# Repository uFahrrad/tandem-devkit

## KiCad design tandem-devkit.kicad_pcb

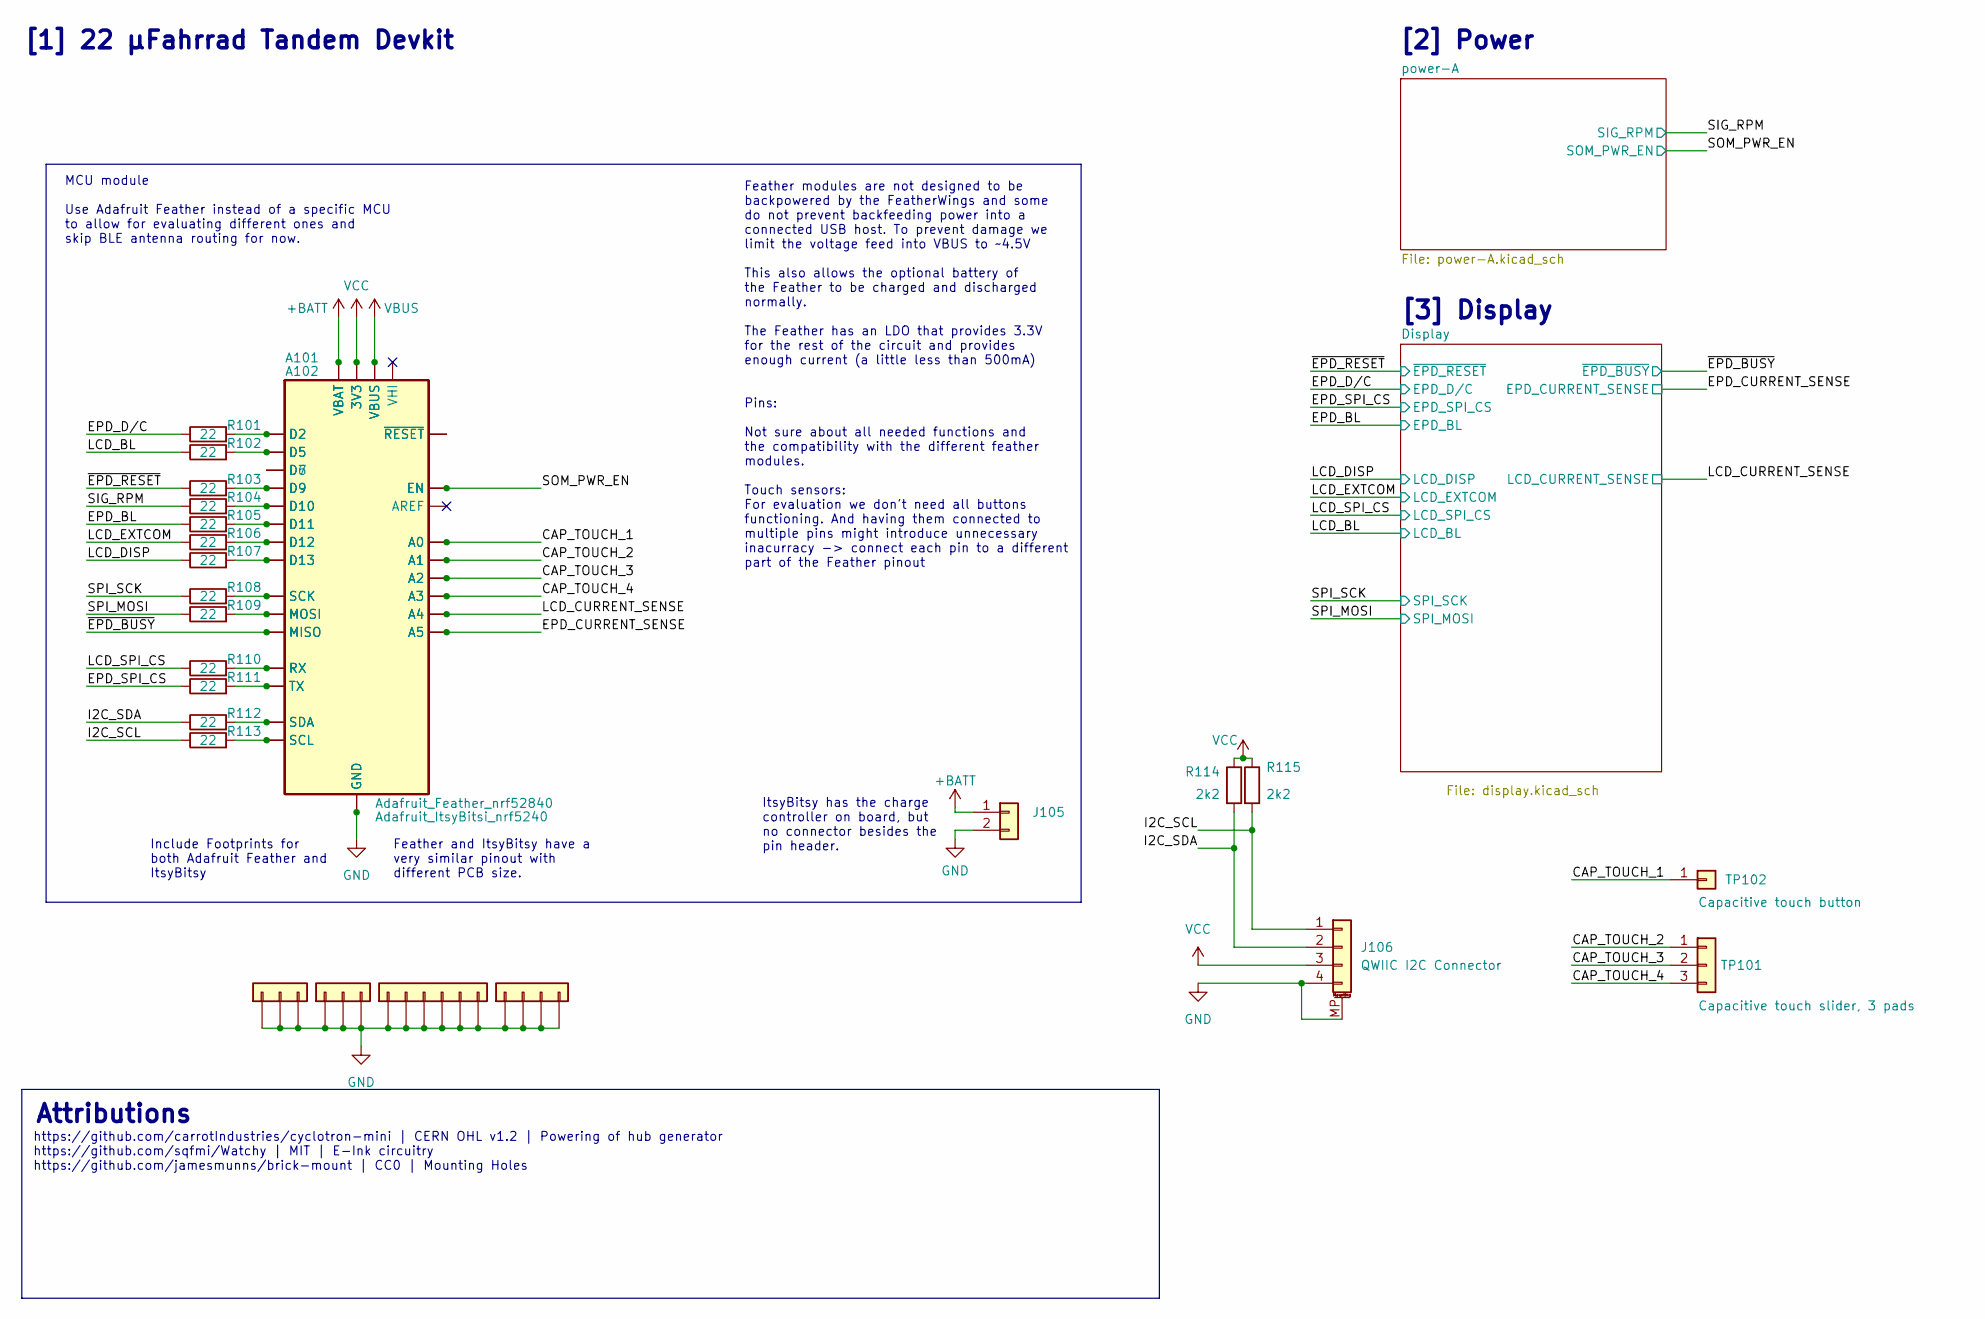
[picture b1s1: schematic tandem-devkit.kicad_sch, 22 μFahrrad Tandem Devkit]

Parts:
A101: Adafruit_ItsyBitsi_nrf5240; Adafruit_ItsyBitsy-nrf52840
A102: Adafruit_Feather_nrf52840; Adafruit_Feather
J101, J102: Conn_01x03; brick-1x3
J103: Conn_01x06; brick-1x6
J104: Conn_01x04; brick-2x2
J105: Conn_01x02; JST_PH_B2B-PH-K_1x02_P2.00mm_Vertical; JLCPCB C173752
J106: QWIIC I2C Connector; JST_SHL_SM04B-SHLS-TF_1x04-1MP_P1.00mm_Horizontal; JLCPCB C145956
R101, R102, R103, R104, R105, R106, R107, R108, R109, R110, R111, R112, R113: 22; R_0603_1608Metric; LCSC C23345
R114, R115: 2k2; R_0603_1608Metric; LCSC C4190
TP101: Capacitive touch slider, 3 pads; TouchSlider-3_30x13mm-covered
TP102: Capacitive touch button; CapBtn_Board_edge

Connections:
+BATT: A101.28 (VBAT), A102.28 (VBAT), J105.1
/CAP_TOUCH_1: A101.5 (A0), A102.5 (A0), TP102.1
/CAP_TOUCH_2: A101.6 (A1), A102.6 (A1), TP101.1; also elsewhere on the board
/CAP_TOUCH_3: A101.7 (A2), A102.7 (A2), TP101.2; also elsewhere on the board
/CAP_TOUCH_4: A101.8 (A3), A102.8 (A3), TP101.3; also elsewhere on the board
/EPD_BL: R105.1; also elsewhere on the board
/EPD_CURRENT_SENSE: A101.10 (A5), A102.10 (A5); also elsewhere on the board
/EPD_D/C: R101.1; also elsewhere on the board
/EPD_SPI_CS: R111.1; also elsewhere on the board
/I2C_SCL: J106.1, R113.1, R115.2
/I2C_SDA: J106.2, R112.1, R114.2
/LCD_BL: R102.1; also elsewhere on the board
/LCD_CURRENT_SENSE: A101.9 (A4), A102.9 (A4); also elsewhere on the board
/LCD_DISP: R107.1; also elsewhere on the board
/LCD_EXTCOM: R106.1; also elsewhere on the board
/LCD_SPI_CS: R110.1; also elsewhere on the board
/SIG_RPM: R104.1; also elsewhere on the board
/SOM_PWR_EN: A101.3 (EN), A102.27 (EN); also elsewhere on the board
/SPI_MOSI: R109.1; also elsewhere on the board
/SPI_SCK: R108.1; also elsewhere on the board
/~EPD_BUSY: A101.13 (MISO), A102.13 (MISO); also elsewhere on the board
/~EPD_RESET: R103.1; also elsewhere on the board
GND: A101.27 (GND), A102.4 (GND), J101.1, J101.2, J101.3, J102.1, J102.2, J102.3, J103.1, J103.2, J103.3, J103.4, J103.5, J103.6, J104.1, J104.2, J104.3, J104.4, J105.2, J106.4, J106.MP (MountPin); also elsewhere on the board
unnamed: A101.1 (~RESET), A102.1 (~RESET)
unnamed: A101.11 (SCK), A102.11 (SCK), R108.2
unnamed: A101.12 (MOSI), A102.12 (MOSI), R109.2
unnamed: A101.14 (D2), A102.16 (D2), R101.2
unnamed: A101.15 (RX), A102.14 (RX), R110.2
unnamed: A101.16 (TX), A102.15 (TX), R111.2
unnamed: A101.17 (SDA), A102.17 (SDA), R112.2
unnamed: A101.18 (SCL), A102.18 (SCL), R113.2
unnamed: A101.19 (D5), A102.19 (D5), R102.2
unnamed: A101.20 (D7), A102.20 (D6)
unnamed: A101.21 (D9), A102.21 (D9), R103.2
unnamed: A101.22 (D10), A102.22 (D10), R104.2
unnamed: A101.23 (D11), A102.23 (D11), R105.2
unnamed: A101.24 (D12), A102.24 (D12), R106.2
unnamed: A101.25 (D13), A102.25 (D13), R107.2
VBUS: A101.26 (VBUS), A102.26 (VBUS); also elsewhere on the board
VCC: A101.2 (3V3), A102.2 (3V3), J106.3, R114.1, R115.1; also elsewhere on the board

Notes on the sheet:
Include Footprints for both Adafruit Feather and ItsyBitsy
ItsyBitsy has the charge controller on board, but no connector besides the pin header.
[2] Power
https://github.com/carrotIndustries/cyclotron-mini | CERN OHL v1.2 | Powering of hub generator https://github.com/sqfmi/Watchy | MIT | E-Ink circuitry https://github.com/jamesmunns/brick-mount | CC0 | Mounting Holes
MCU module Use Adafruit Feather instead of a specific MCU to allow for evaluating different ones and skip BLE antenna routing for now.
[3] Display
Attributions
Feather and ItsyBitsy have a very similar pinout with different PCB size.
Pins: Not sure about all needed functions and the compatibility with the different feather modules. Touch sensors: For evaluation we don't need all buttons functioning. And having them connected to multiple pins might introduce unnecessary inacurracy -> connect each pin to a different part of the F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
[1] 22 μFahrrad Tandem Devkit
Feather modules are not designed to be backpowered by the FeatherWings and some do not prevent backfeeding power into a connected USB host. To prevent damage we limit the voltage feed into VBUS to ~4.5V This also allows the optional battery of the Feather to be charged and discharged normally. The 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

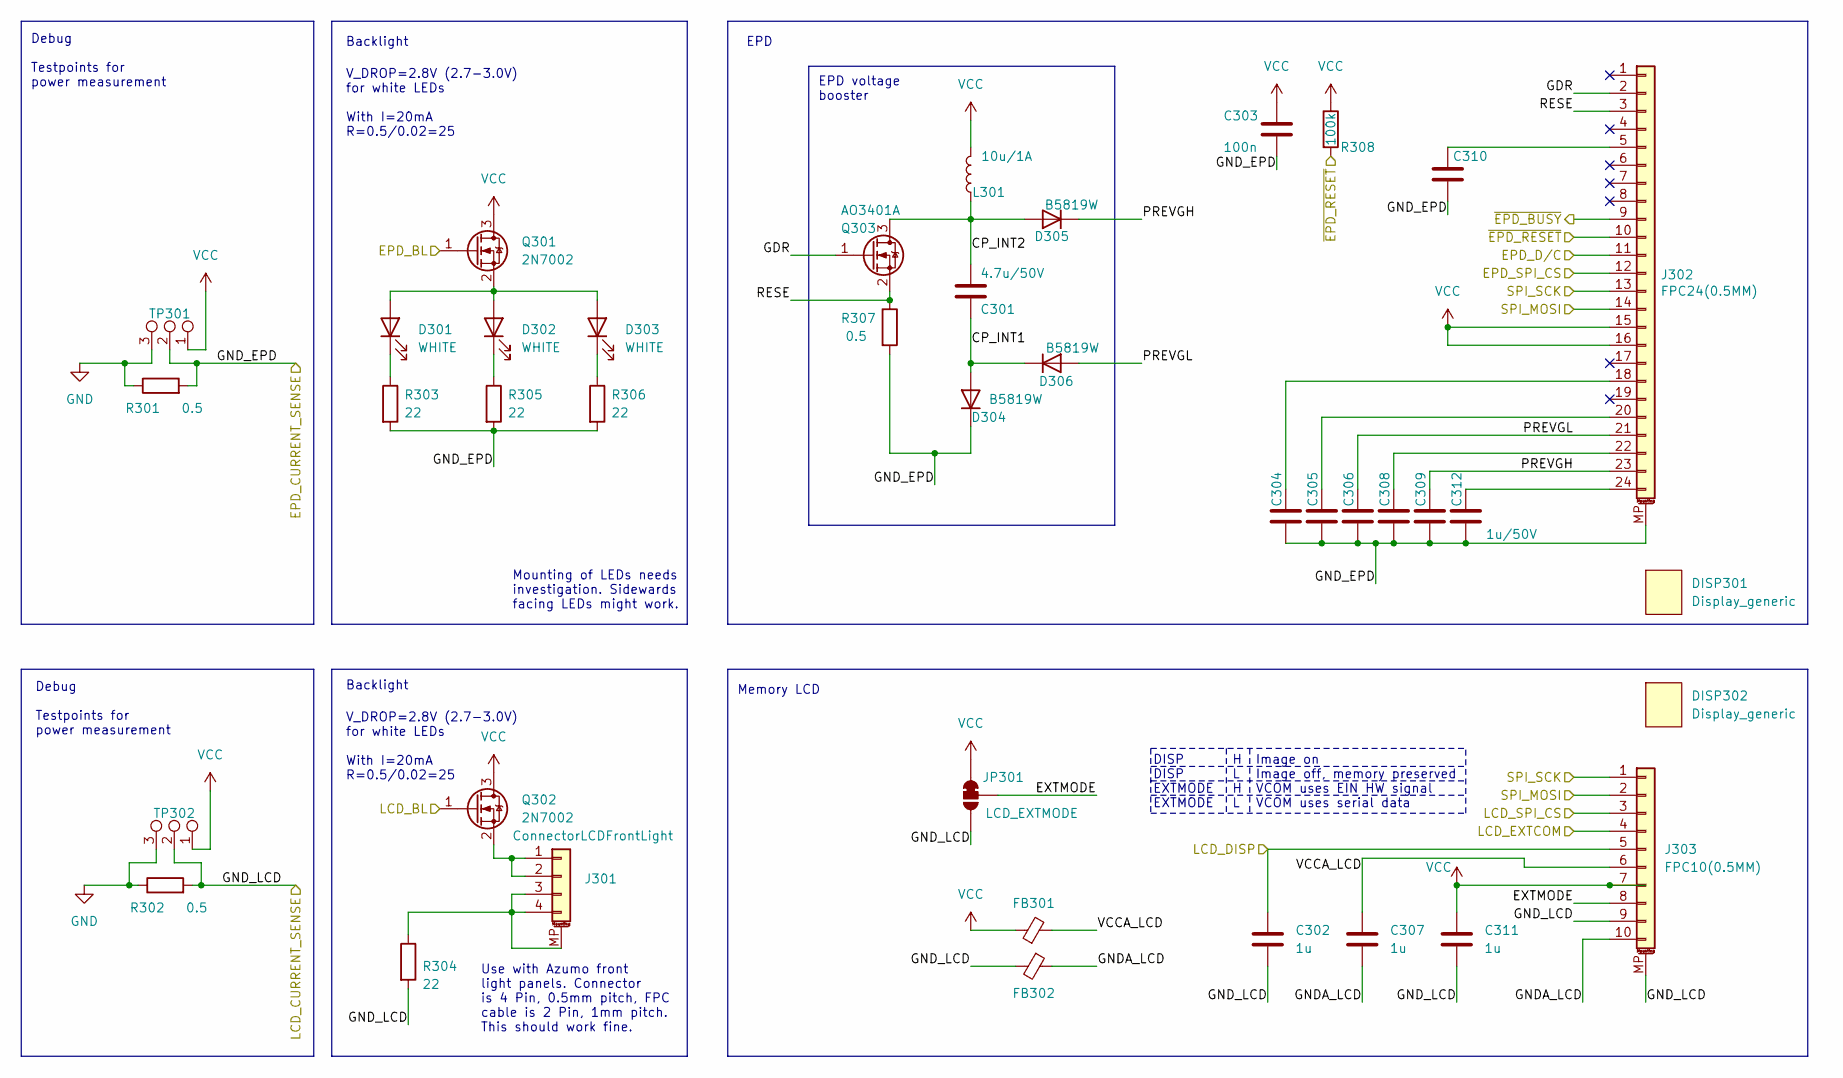
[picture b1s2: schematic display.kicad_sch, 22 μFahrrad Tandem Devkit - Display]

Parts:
C301: 4.7u/50V; C_1206_3216Metric; LCSC C29823
C302, C307, C311: 1u; C_0603_1608Metric; LCSC C15849
C303: 100n; C_0603_1608Metric; LCSC C14663
C304, C305, C306, C308, C309, C310, C312: 1u/50V; C_0603_1608Metric; LCSC C15849
D301, D302, D303: WHITE; LED_sidemount_C205440; JLCPCB C965863
D304, D305, D306: B5819W; D_SOD-123; JLCPCB C8598
DISP301, DISP302: Display_generic; 154_Epaper_Display
FB301, FB302: FerriteBead_Small; R_0805_2012Metric; JLCPCB C1017
J301: ConnectorLCDFrontLight; jlcpcb-C11047_FFC_1x04-1MP_P0.50mm_Horizontal; JLCPCB C11047
J302: FPC24(0.5MM); jlcpcb-C11057_FFC_1x24-1MP_P0.50mm_Horizontal; JLCPCB C11057
J303: FPC10(0.5MM); jlcpcb-C11050_FFC_1x10-1MP_P0.50mm_Horizontal; JLCPCB C11050
JP301: LCD_EXTMODE; SolderJumper-3_P1.3mm_Bridged12_RoundedPad1.0x1.5mm
L301: 10u/1A; L_4.0x4.0_H3; JLCPCB C38117
Q301, Q302: 2N7002; SOT-23; JLCPCB C8545
Q303: AO3401A; SOT-23; JLCPCB C15127
R301, R302: 0.5; R_0805_2012Metric; JLCPCB C25271
R303, R304, R305, R306: 22; R_0603_1608Metric; LCSC C23345
R307: 0.5; R_0805_2012Metric; LCSC C28319
R308: 100k; R_0603_1608Metric; LCSC C25803
TP301, TP302: TestPoint_3Pole; TestPoint_1x03_P1.27mm

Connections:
/Display/CP_INT1: C301.2, D304.2 (A), D306.1 (K)
/Display/CP_INT2: C301.1, D305.2 (A), L301.1, Q303.3 (D)
/Display/EXTMODE: J303.8, JP301.2 (C)
/Display/GDR: J302.2, Q303.1 (G)
/Display/GNDA_LCD: C307.2, FB302.1, J303.10
/Display/PREVGH: C309.2, D305.1 (K), J302.23
/Display/PREVGL: C306.2, D306.2 (A), J302.21
/Display/RESE: J302.3, Q303.2 (S), R307.1
/Display/VCCA_LCD: C307.1, FB301.2, J303.6
/EPD_BL: Q301.1 (G); also elsewhere on the board
/EPD_CURRENT_SENSE: C303.2, C304.1, C305.1, C306.1, C308.1, C309.1, C310.2, C312.1, D304.1 (K), J302.MP (MountPin), R301.2, R303.2, R305.2, R306.2, R307.2, TP301.2; also elsewhere on the board
/EPD_D/C: J302.11; also elsewhere on the board
/EPD_SPI_CS: J302.12; also elsewhere on the board
/LCD_BL: Q302.1 (G); also elsewhere on the board
/LCD_CURRENT_SENSE: C302.2, C311.2, FB302.2, J303.9, J303.MP (MountPin), JP301.3 (B), R302.2, R304.2, TP302.2; also elsewhere on the board
/LCD_DISP: C302.1, J303.5; also elsewhere on the board
/LCD_EXTCOM: J303.4; also elsewhere on the board
/LCD_SPI_CS: J303.3; also elsewhere on the board
/SPI_MOSI: J302.14, J303.2; also elsewhere on the board
/SPI_SCK: J302.13, J303.1; also elsewhere on the board
/~EPD_BUSY: J302.9; also elsewhere on the board
/~EPD_RESET: J302.10, R308.2; also elsewhere on the board
GND: R301.1, R302.1, TP301.3, TP302.3; also elsewhere on the board
unnamed: C304.2, J302.18
unnamed: C305.2, J302.20
unnamed: C308.2, J302.22
unnamed: C310.1, J302.5
unnamed: C312.2, J302.24
unnamed: D301.1 (K), R303.1
unnamed: D301.2 (A), D302.2 (A), D303.2 (A), Q301.2 (S)
unnamed: D302.1 (K), R305.1
unnamed: D303.1 (K), R306.1
unnamed: J301.1, J301.2, Q302.2 (S)
unnamed: J301.3, J301.4, J301.MP (MountPin), R304.1
VCC: C303.1, C311.1, FB301.1, J302.15, J302.16, J303.7, JP301.1 (A), L301.2, Q301.3 (D), Q302.3 (D), R308.1, TP301.1, TP302.1; also elsewhere on the board

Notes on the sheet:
Image on Image off, memory preserved VCOM uses EIN HW signal VCOM uses serial data
H L H L
V_DROP=2.8V (2.7-3.0V) for white LEDs With I=20mA R=0.5/0.02=25
Use with Azumo front light panels. Connector is 4 Pin, 0.5mm pitch, FPC cable is 2 Pin, 1mm pitch. This should work fine.
Debug Testpoints for power measurement
Mounting of LEDs needs investigation. Sidewards facing LEDs might work.
Backlight
EPD
DISP DISP EXTMODE EXTMODE
Memory LCD
EPD voltage booster

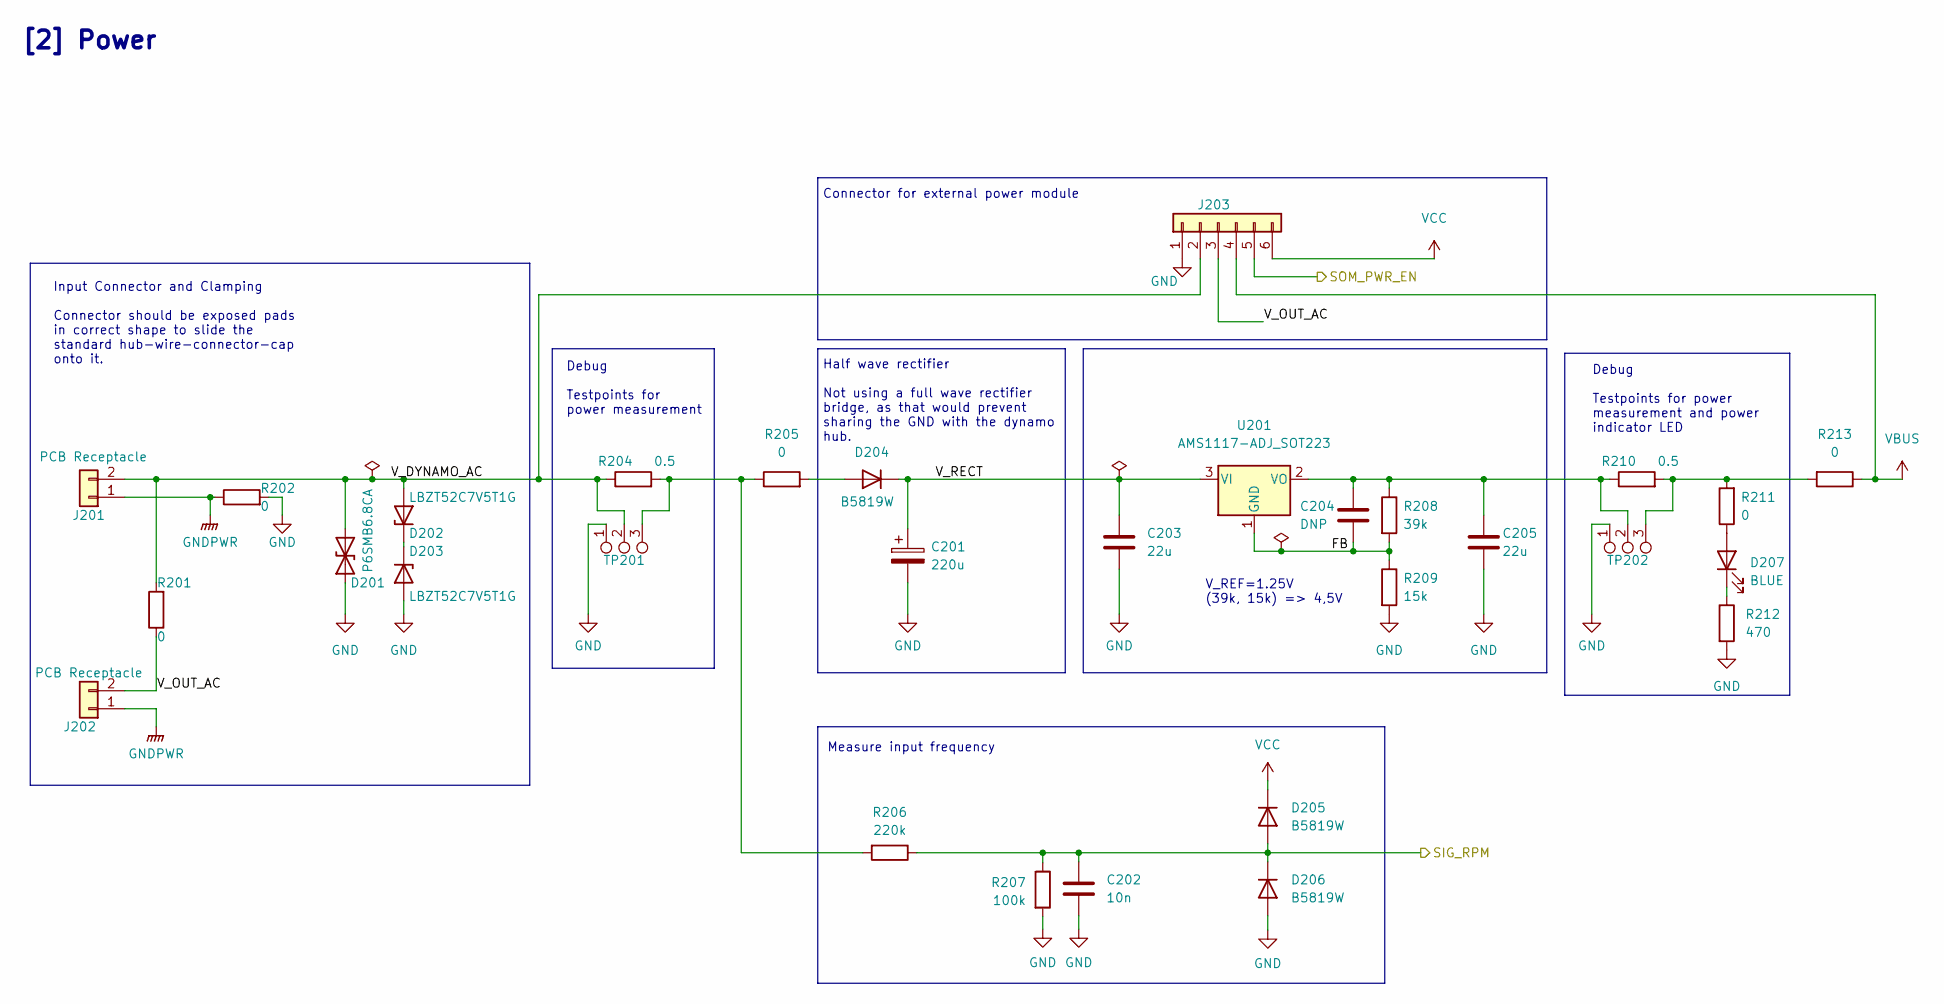
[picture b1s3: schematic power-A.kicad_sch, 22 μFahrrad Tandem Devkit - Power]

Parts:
C201: 220u; CP_EIA-7343-43_Kemet-X; JLCPCB C117040
C202: 10n; C_0603_1608Metric; LCSC C57112
C203, C205: 22u; C_1206_3216Metric; JLCPCB C12891
C204: DNP; C_0603_1608Metric
D201: P6SMB6.8CA; D_SMB; JLCPCB C78395
D202, D203: LBZT52C7V5T1G; D_SOD-123; JLCPCB C12760
D204, D205, D206: B5819W; D_SOD-123; JLCPCB C8598
D207: BLUE; LED_0603_1608Metric; JLCPCB C2293
J201, J202: PCB Receptacle; shimano-hub-generator-connector
J203: Conn_01x06; powermodule
R201, R202, R205, R211, R213: 0; R_0805_2012Metric_Pad1.20x1.40mm_HandSolder; LCSC C17477
R204, R210: 0.5; R_0805_2012Metric; JLCPCB C25271
R206: 220k; R_0603_1608Metric; LCSC C22961
R207: 100k; R_0603_1608Metric; LCSC C25803
R208: 39k; R_0603_1608Metric; LCSC C23153
R209: 15k; R_0603_1608Metric; LCSC C22809
R212: 470; R_0603_1608Metric; LCSC C23179
TP201, TP202: TestPoint_3Pole; TestPoint_1x03_P1.27mm
U201: AMS1117-ADJ_SOT223; SOT-223-3_TabPin2; JLCPCB C347224

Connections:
/SIG_RPM: C202.1, D205.2 (A), D206.1 (K), R206.1, R207.1; also elsewhere on the board
/SOM_PWR_EN: J203.5; also elsewhere on the board
/power-A/FB: C204.2, R208.2, R209.1, U201.1 (GND)
/power-A/V_DYNAMO_AC: D201.2 (A2), D202.2 (A), J201.2, J203.2, R201.2, R204.1, TP201.2
/power-A/V_OUT_AC: J202.2, J203.3, R201.1
/power-A/V_RECT: C201.1, C203.1, D204.1 (K), U201.3 (VI)
GND: C201.2, C202.2, C203.2, C205.2, D201.1 (A1), D203.2 (A), D206.2 (A), J203.1, R202.2, R207.2, R209.2, R212.2, TP201.1, TP202.1; also elsewhere on the board
GNDPWR: J201.1, J202.1, R202.1
unnamed: C204.1, C205.1, R208.1, R210.1, TP202.2, U201.2 (VO)
unnamed: D202.1 (K), D203.1 (K)
unnamed: D204.2 (A), R205.2
unnamed: D207.1 (K), R212.1
unnamed: D207.2 (A), R211.1
unnamed: R204.2, R205.1, R206.2, TP201.3
unnamed: R210.2, R211.2, R213.2, TP202.3
VBUS: J203.4, R213.1; also elsewhere on the board
VCC: D205.1 (K), J203.6; also elsewhere on the board

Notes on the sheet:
Debug Testpoints for power measurement
V_REF=1.25V (39k, 15k) => 4,5V
Connector for external power module
Debug Testpoints for power measurement and power indicator LED
Half wave rectifier Not using a full wave rectifier bridge, as that would prevent sharing the GND with the dynamo hub.
Measure input frequency
Input Connector and Clamping Connector should be exposed pads in correct shape to slide the standard hub-wire-connector-cap onto it.
[2] Power

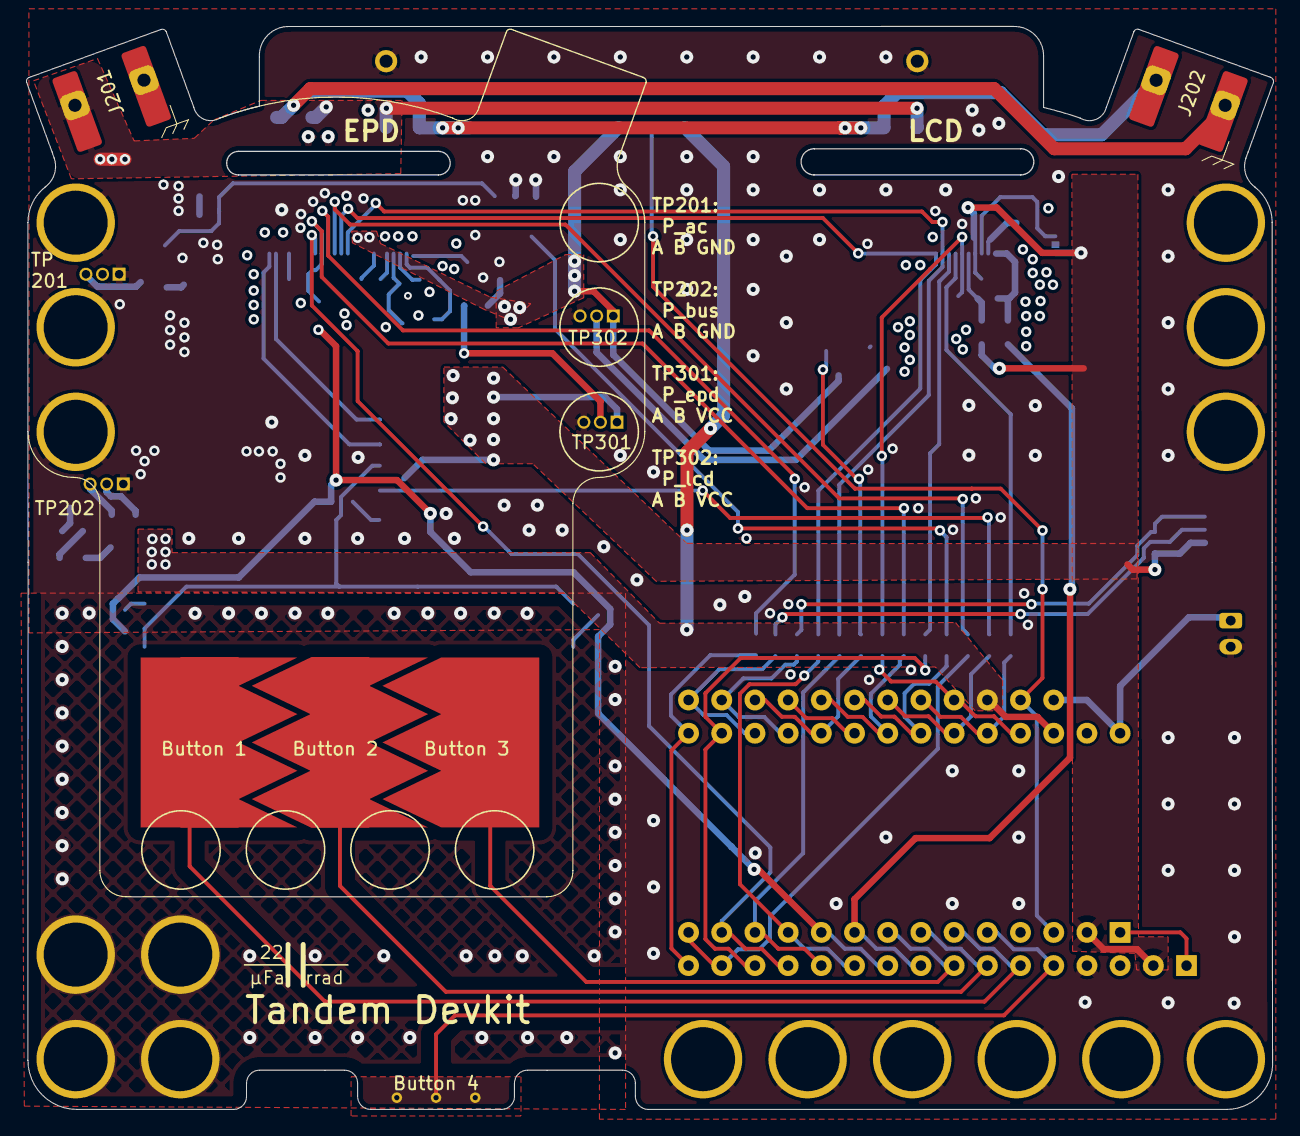
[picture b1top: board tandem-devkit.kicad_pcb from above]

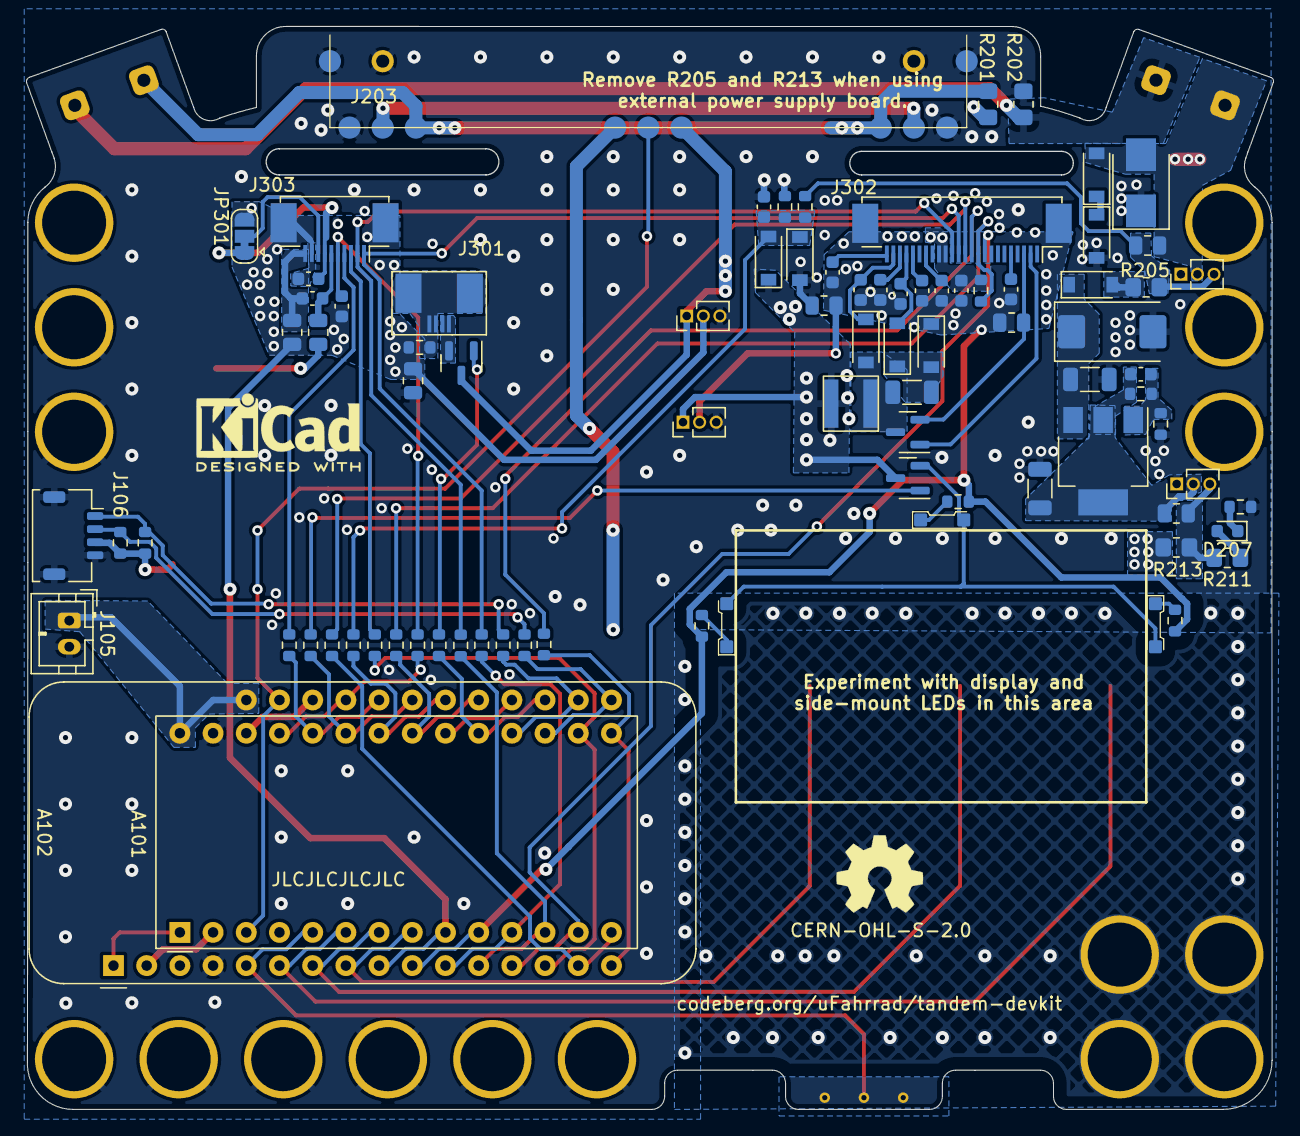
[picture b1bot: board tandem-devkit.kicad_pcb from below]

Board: 4 copper layers, 95.4 x 82.9 mm, 99 parts (91 on the bottom side), 72 nets.

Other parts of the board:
22uFahrrad-Logo: LOGO
BoardOutline: μFahrrad-DevTandem-Shape
KiCAD-Logo: KiCad-Logo2_5mm_SilkScreen
OSHW-Logo: OSHW-Symbol_6.7x6mm_SilkScreen
locked: Capacitive touch slider, 3 pads; TouchSlider-3_30x13mm-covered

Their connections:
/CAP_TOUCH_2: locked.1; also elsewhere on the board
/CAP_TOUCH_3: locked.2; also elsewhere on the board
/CAP_TOUCH_4: locked.3; also elsewhere on the board

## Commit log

2022-06-10 Initial Commit with kicad-git-filters setup
2022-06-10 Add gitignore
2022-06-10 Add kicad_pcb-diff tooling
2022-06-10 gitignore autosave files
2022-06-10 Addd schematic
2022-06-10 Add WIP PCB layout
2022-06-10 Add project library
2022-06-10 Add project PATH configuration files
2022-06-10 Add project file
2022-06-20 gitginore kicad_prl file
2022-06-20 Fixup difffilters
2022-06-20 futher small chnages.
2022-06-20 ERC: allow multiple net names for display GND/current_sense nets
2022-06-20 footprints: add mounting pins to FPC connectors
2022-06-20 Schematics: Add mountingpins to connectors, remove ERC warnings for alternate parts
2022-06-20 Pre routing: footprints&parts
2022-06-20 gitignore: ignore more backup files
2022-06-20 PCB: rough placement, 1/x
2022-06-20 PCB: include schematic changes
2022-06-20 schematic: add placeholders for the actual displays
    Also fixup GND_LCD for Extmode SolderJumper.
2022-06-20 schematic: GND_EPD fixups
2022-06-20 footprints: fixup courtyard of inductors
2022-06-20 schematic: replace LCD Light with connector for Azumo light panel
2022-06-20 footprints: add needed footprints for backlight LED and connector
2022-06-20 schematic: fix LCD VCCA decoupling capacitor
2022-06-20 PCB: sync with schematic
2022-06-20 PCB: flip feather so it can be soldered directly underneath the board
2022-06-20 PCB: reorder a little, move all feather/itsy-bitsy internal connections to single copper layer
2022-06-20 schematic: fixup reference designator positions
2022-06-20 prepare for touch button routing
2022-06-20 PCB: rough placement, 2/x
2022-06-20 PCB: routing mostly done
2022-06-20 PCB: update netlist
2022-06-20 PCB: align testpoint orientation with silkscreen
2022-06-20 Mark some parts as 'exclude from bom'
2022-06-20 gitignore: ignore even more backup files
2022-06-20 PCB: Touchbuttons and silkscreen adaptions
2022-06-20 PCB: add GND stitching vias
2022-06-20 schematic: cleanups and diode selection
2022-06-20 PCB: fix most of zone priorities and connections
2022-06-20 Schematic: BOM consolidation and JLCPCB part no annotation
2022-06-20 schematic: assign connector footprint
2022-06-20 PCB: route display connectors
2022-06-20 schematic: change i2c pull-ups to 2k2
    As mentioned as "Phil's Lab" mentions as his suggested value
2022-06-20 fixups for silkscreen and 'exclude from bom'
2022-06-20 move power module intput directly to V_DYNAMO_AC to ease routing
2022-06-20 schematic: switch EPD/LCD current sense lines to ease routing
2022-06-20 PCB: route cap buttons and adjust zones
2022-06-20 footprints: define testpoint with smaller courtyard
2022-06-20 Exchange brick-mount holes with actual footprint, connect holes to gnd
2022-06-20 PCB/footprints: Update shape and connector
2022-06-20 PCB: import JLCPCB 4-Layer board settings
2022-06-20 PCB: fix DRC
    - reduced track clearance for power and default net to fit between
    the pads of connectors
    - rearranged epaper driver to adhere to DRC rules
    - connected Feather and ItsyBitsy footprint and the related resistors
2022-06-20 Components: select JLCPCB basic components
2022-06-20 Ficup column name for JLCPCB/LCSC part no
2022-06-20 Schematic: more 0R resistors and power module connector
2022-06-20 PCB: adapt GND zone to board
2022-06-20 PCB: rough placement, 3/x
2022-06-20 connect everything except the capacitive touch sensors
2022-06-20 Footprints: add forgotten footprints to git
2022-06-20 PCB: add powermodule and reroute some stuff
2022-06-20 PCB: resolve silkscreen/via overlap
2022-06-20 PCB: prepare JLC parts list for manufacturing
2022-06-20 schematic: add another capacitive touch point, reorder feather pins
2022-06-20 PCB: move components out of brickmount courtyards
2022-06-20 PCB: flip brickmount footprints so courtyard applies to back of PCB
2022-06-20 PCB: add logos and URL
2022-06-20 PCB: pull updates from schematic
2022-06-20 Add LICENCE file
2022-06-20 Update drawing sheets title block
2022-06-20 PCB: mark logos as not-in-schematic
2022-06-20 schematic: rearrange main page a little
2022-06-20 PCB: add designator for JLC order number
2022-06-20 exchange C to polarized
2022-06-20 exchange backlight LED for one that is actually white and available
2022-06-21 PCB: update zones
2022-06-21 update power indicator LED to match JLC coponent
2022-06-21 PCB/footprints: fix up FPC connectors
2022-06-21 meta: add github action for keeping mirror up to date
2022-06-22 Revert "meta: add github action for keeping mirror up to date"
    This reverts commit 79af080966d0dfccbd1cf98be5fe91daaca357ea.
    Switched to using an external repo in the same github organization to
    keep the mirrors updated, so this is not needed anymore.

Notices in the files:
display.kicad_sch:
CERN Open Hardware Licence Version 2 - Strongly Reciprocal
CERN-OHL-S-2.0 https://spdx.org/licenses/CERN-OHL-S-2.0.html
tandem-devkit.kicad_pcb:
CERN-OHL-S-2.0
